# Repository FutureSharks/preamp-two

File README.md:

# Preamp Two

Here is my Hi-Fi preamplifier project. In this repository you can find schematics, PCB layouts, CircuitPython code, BoMs, measurements and photos.

Features:

* MDAC volume controller
* 6 way relay based input selector
* High performance design with measurements
* Quality components and modular design
* Completely digitally controlled
* All open source and written in Python

## Components and code

The preamplifier is made up of a number of connected components:

* MDAC attenuator ([PCB](PCBs/mdac-attenuator), [code](code/modules/mdac_attenuator.py)): Controls the volume
* Input selector ([PCB](PCBs/input-selector), [code](code/modules/input_selector.py)): Selects the input
* Encoder panel ([PCB](PCBs/encoder-panel), [code](code/modules/encoder_panel.py)): Holds rotary encoder and LED indicator ring
* Power Supply 5V ([PCB](PCBs/psu-digital)): Power supply for digital components.
* Power Supply +/- 15V ([PCB](PCBs/psu-analog)): Analog Power supply for MDAC attenuator
* Micro controller board ([PCB](PCBs/mcu-board), [code](code/main.py)): Holds the [Itsy Bitsy M4 Express](https://learn.adafruit.com/introducing-adafruit-itsybitsy-m4?view=all) and other connectors
* RCA panel ([PCB](PCBs/rca-panel)): For the RCA sockets and connectors

The PCBs and schematics were created in [KiCad](http://kicad.org/) and the code that runs on the micro controller is [CircuitPython](https://circuitpython.org/).

## Enclosure

Diagrams, CAD files and other information can be found here: [enclosure](enclosure)

## Measurements

THD, S/N ratio and power consumption: [measurements](measurements)

## Prototypes and testing

See here for a number of different [prototypes](prototypes). All PCBs were made by [OSH Park](https://oshpark.com/).

## Photos

---

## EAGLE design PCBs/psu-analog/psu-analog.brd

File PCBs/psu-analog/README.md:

# Analog Power Supply

This the +/- 15V power supply. It powers the op-amp in the MDAC attenuator using TPS7A3301 regulators.

The PCB files are in Eagle format.

## Photos

## Schematic

## Layout

## BoM

|  Part name | RS part          | Farnell Part | Mouser Part          | Description                                                     | EVM Part name | Notes                |
| ---------- | ---------------- | ------------ | -------------------- | --------------------------------------------------------------- | ------------- | -------------------- |
| C1/C2      | 571319           |              | 667-EEU-FC1V182S     | Large input cap, 7.5mm/18mm                                     | -             |                      |
| C5/C6      | -                |              | 80-C1206C104K5R      | 1206, 0.1uF, X5R or X7R                                         | -             |                      |
| C7/C8      | 7900610          |              | 81-GRM31CR61H106KA2L | 1206, 47uF, X5R or X7R, 2220 package                            | C1            |                      |
| C3A/B      | 7236657          |              | 81-GRM31MR71H105KA88 | 1206, 1uF, X5R or X7R                                           | C3            | NR/SS                |
| C4A/B      | 2644141          |              | 80-C1206C103K1R      | 1206, 10nF/0.01uF, X5R or X7R                                   | C4            | CFF/CBYP             |
| C9-14      | 7900610          |              | 81-GRM31CR61H106KA2L | 1206, 22-15uF, multiple, 2220 package                           | C5-C9         | Total at least 47uF  |
| C15/C16    | 571408 or 571290 |              | 667-EEU-FC1E102      | Large output cap, 5mm/13mm                                      | C10           |                      |
| R1A/B      |                  |              | 667-ERJ-8ENF1244V    | 1.24M                                                           | R1            | Value for -15VDC     |
| R2A/B      |                  |              | 667-ERJ-8ENF1053V    | 105K                                                            | R2            | Value for -15VDC     |
| B1/2       | 8148800          | 1336500      | 625-DFL1508S-E3/77   | VISHAY - DFL1508S-E3/45, BRIDGE RECTIFIER                       |               |                      |
| IC1/IC2    |                  |              | 595-TPS7A3301KC      | LDO Voltage Regulators -3 to -36V,-1A,Ultra Low Noise,High PSRR |               |                      |
| TR1        | 2239216          |              |                      | Block FL6/FL8, Talema/Amveco 5/7VA or standard EI-42            |               |                      |
| F1         | 7874164          |              | 576-64900001039      | 5x20mm Fuseholder 6.3A 250V                                     |               |                      |
| AC         | 403932           |              |                      | 5.08mm Pitch 2 Way 1 Row Straight PCB Header                    |               | AC in                |
| KK1/KK2    |                  |              | 532-513002B25G       |                                                                 |               | Heatsinks, SK104-PAD |
| LED        | -                | -            | -                    | Any 1206 LED                                                    |               |                      |
| RLED       | -                | -            | -                    | To match LEDs                                                   |               |                      |
| X2         |                  |              |                      |                                                                 |               | Power out            |
| Fuse       |                  |              | 530-5ST63-R          | 5x20mm, 63mA                                                    |               |                      |

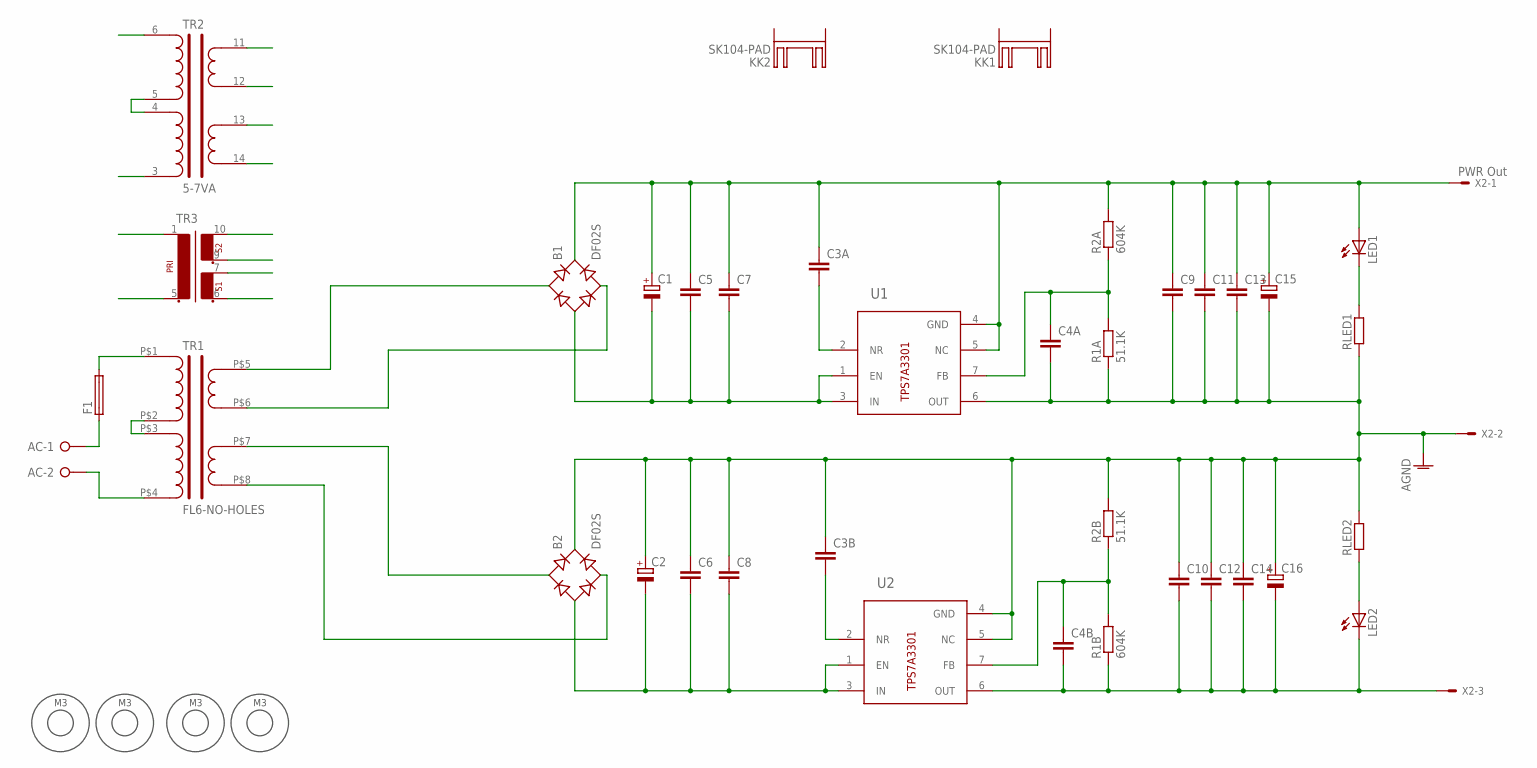
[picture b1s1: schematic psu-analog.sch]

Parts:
AC: W237-02P; W237-132
B1, B2: DF02S; DFS
C1, C2: CPOL-EUE7.5-18; E7,5-18
C3A, C3B, C4A, C4B, C5, C6, C7, C8, C9, C10, C11, C12, C13, C14: C-EUC1206; C1206
C15, C16: CPOL-EUE5-13; E5-13
F1: GSH15
KK1, KK2: SK104-PAD
LED1, LED2: LEDSMT1206; 1206
R1A, R2B: 51.1K; R1206
R1B, R2A: 604K; R1206
RLED1, RLED2: R-EU_R1206; R1206
TR1: FL6-NO-HOLES
TR2: 5-7VA; 5_7VA-PC
TR3: EI42-2
U1, U2: TPS7A3301KC-OTHER-PACKAGE; 7TO-220-OTHER
U$1, U$2, U$3, U$4: M3_HOLE
X2: PWR Out; 22-23-2031

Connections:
AGND: B2.+, C2.+, C3B.1, C4A.2, C6.1, C8.1, C9.2, C10.1, C11.2, C12.1, C13.2, C14.1, C15.-, C16.+, R1A.1, R2B.2, RLED1.1, RLED2.2, U1.6 (OUT), U2.4 (GND), U2.5 (NC), X2.2
unnamed: TR1.P$2 (PRI1B), TR1.P$3 (PRI2A), TR2.4, TR2.5
unnamed: F1.2, TR1.P$1 (PRI1A), TR2.6, TR3.1
unnamed: AC.2, TR1.P$4 (PRI2B), TR2.3, TR3.5 (2)
unnamed: AC.1, F1.1
unnamed: LED2.A, RLED2.1
unnamed: LED1.C, RLED1.2
unnamed: C4A.1, R1A.2, R2A.1, U1.7 (FB)
unnamed: C3B.2, U2.2 (NR)
unnamed: C4B.1, R1B.2, R2B.1, U2.7 (FB)
unnamed: B1.AC2, TR1.P$6 (SEC1B), TR2.12, TR3.9 (5)
unnamed: B1.AC1, TR1.P$5 (SEC1A), TR2.11, TR3.10 (6)
unnamed: B2.AC2, TR1.P$8 (SEC2B), TR2.14, TR3.6 (3)
unnamed: C3A.2, U1.2 (NR)
unnamed: B2.AC1, TR1.P$7 (SEC2A), TR2.13, TR3.7 (4)
unnamed: C4B.2, C10.2, C12.2, C14.2, C16.-, LED2.C, R1B.1, U2.6 (OUT), X2.3
unnamed: B1.+, C1.+, C3A.1, C5.1, C7.1, C9.1, C11.1, C13.1, C15.+, LED1.A, R2A.2, U1.4 (GND), U1.5 (NC), X2.1
VIN+: B1.-, C1.-, C5.2, C7.2, U1.1 (EN), U1.3 (IN)
VIN-: B2.-, C2.-, C6.2, C8.2, U2.1 (EN), U2.3 (IN)

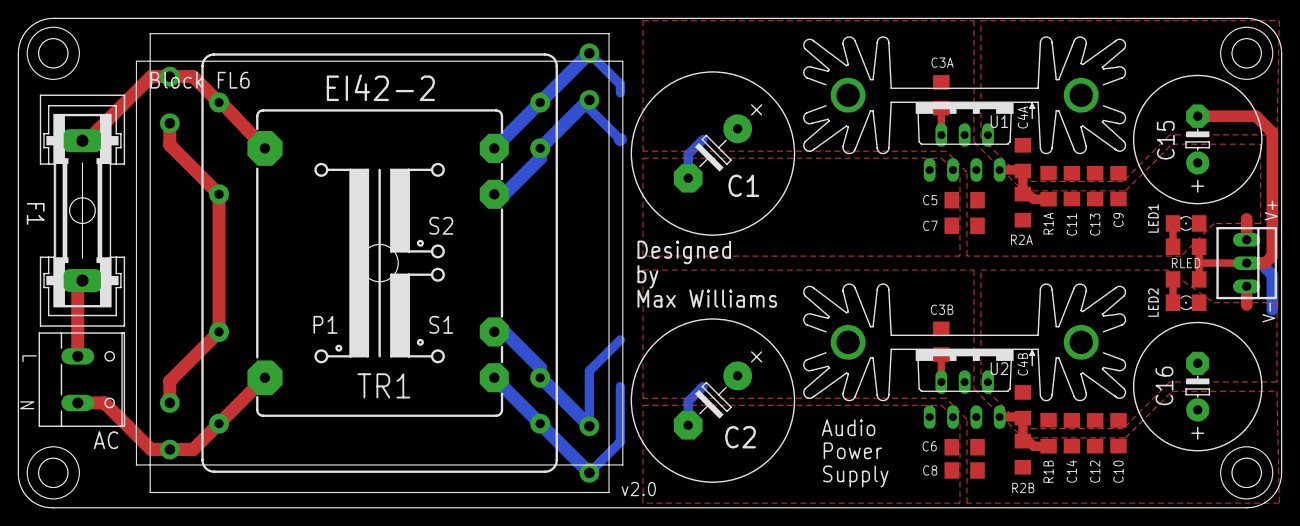
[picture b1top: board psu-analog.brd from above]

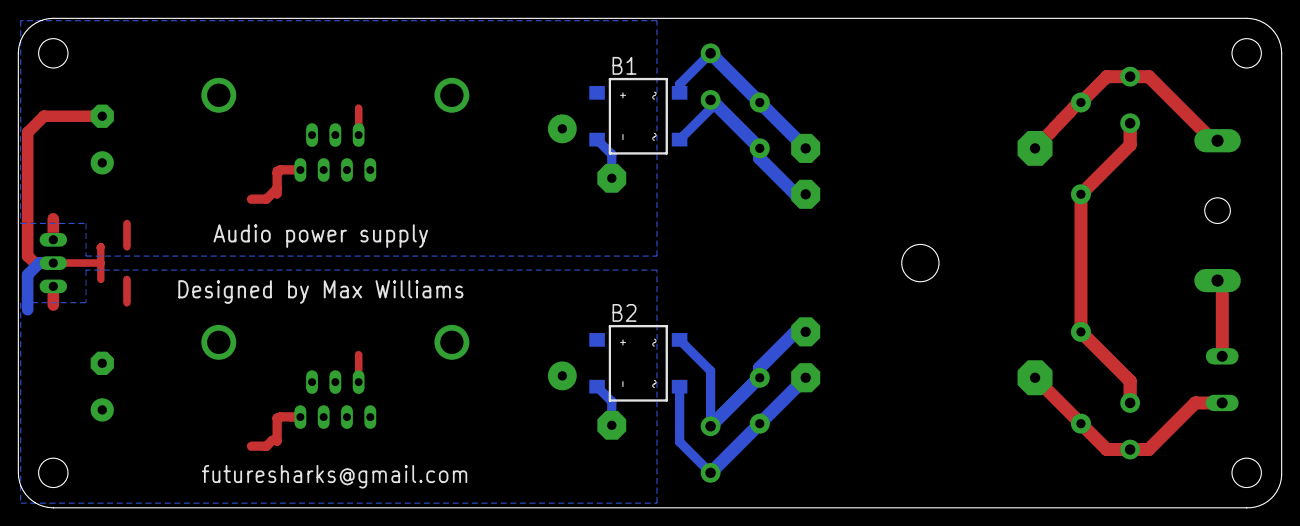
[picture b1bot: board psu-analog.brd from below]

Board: 2 copper layers, 137.7 x 53.3 mm, 42 parts (2 on the bottom side), 19 nets.

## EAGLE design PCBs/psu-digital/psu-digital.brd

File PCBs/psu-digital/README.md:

# Digital Power Supply

This the 5V digital power supply. It powers the input selector, digital part of the MDAC attenuator, the NeoPixels in the encoder panels and the encoders.

It uses a LT1763 regulator.

The PCB files are in Eagle format.

## Photos

## Schematic

## Layout

## BoM

| Reference   | Footprint / Notes  |
|-------------|--------------------|
| F1 | Fuse holder. |
| TR1 | Pads for Block FL2/FL4/FL6/FL8 or EI38 or EI30. Ideally 2x 6VAC. |
| B1 | VISHAY DFL1508S bridge rectifier. |
| C1 | Panasonic FC 1500UF, 16V. |
| L1 | INDUCTOR, 1210 CASE, 10UH. |
| L2 | FERRITE BEAD, 0.1OHM, 2A, 1206. |
| C2 | 100nF X7R, 1206 package. |
| IC1 | LT1763CS8-5, 5V fixed regulator. |
| C3 | C0G/NP0, 10NF, 100V, 1206 package. |
| C4 | Panasonic FK 100UF, 6.3V, SMD. |
| C5 | 100nF X7R, 1206 package. |
| R1 | Resistor for LED, 1206 package. |
| LED | 1206 LED |

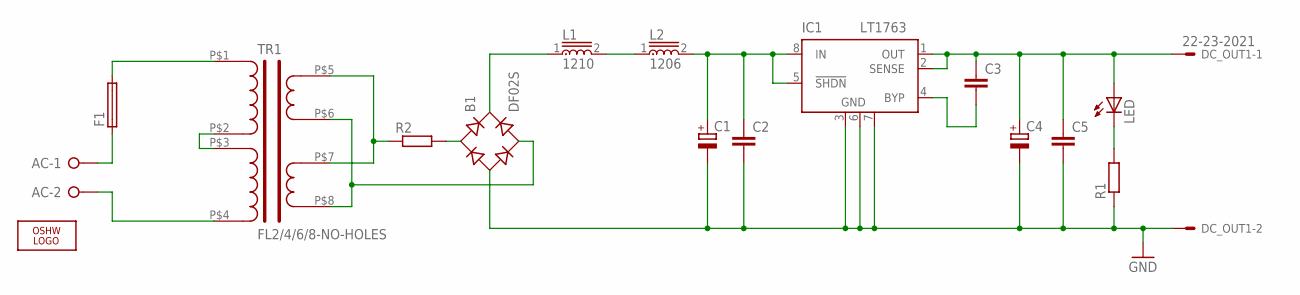
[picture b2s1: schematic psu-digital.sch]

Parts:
AC: W237-02P; W237-132
B1: DF02S; DFS
C1: CPOL-EUE7.5-16; E7,5-16
C2, C3, C5: C-EUC1206; C1206
C4: CPOL-EUD; PANASONIC_D
DC_OUT1: 22-23-2021
F1: GSH15
IC1: LT1763; SOIC8
L1: 1210
L2: 1206
LED: LEDCHIPLED_1206; CHIPLED_1206
LOGO1: OSHW_LOGO_FILLX0200-NT; OSHW_FILLX200_NOTEXT
R1: R-EU_R1206; R1206
R2: R-EU_R1210; R1210
TR1: FL2/4/6/8-NO-HOLES

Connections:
GND: B1.-, C1.-, C2.2, C4.-, C5.2, DC_OUT1.2, IC1.3 (GND), IC1.6 (GND), IC1.7 (GND), R1.1
unnamed: TR1.P$2 (PRI1B), TR1.P$3 (PRI2A)
unnamed: F1.2, TR1.P$1 (PRI1A)
unnamed: AC.2, TR1.P$4 (PRI2B)
unnamed: AC.1, F1.1
unnamed: R2.1, TR1.P$5 (SEC1A), TR1.P$7 (SEC2A)
unnamed: B1.AC1, R2.2
unnamed: C3.2, IC1.4 (BYP)
unnamed: LED.C, R1.2
unnamed: B1.+, L1.1
unnamed: C3.1, C4.+, C5.1, DC_OUT1.1, IC1.1 (OUT), IC1.2 (SENSE), LED.A
unnamed: L1.2, L2.1
unnamed: B1.AC2, TR1.P$6 (SEC1B), TR1.P$8 (SEC2B)
unnamed: C1.+, C2.1, IC1.5 (!SHDN), IC1.8 (IN), L2.2

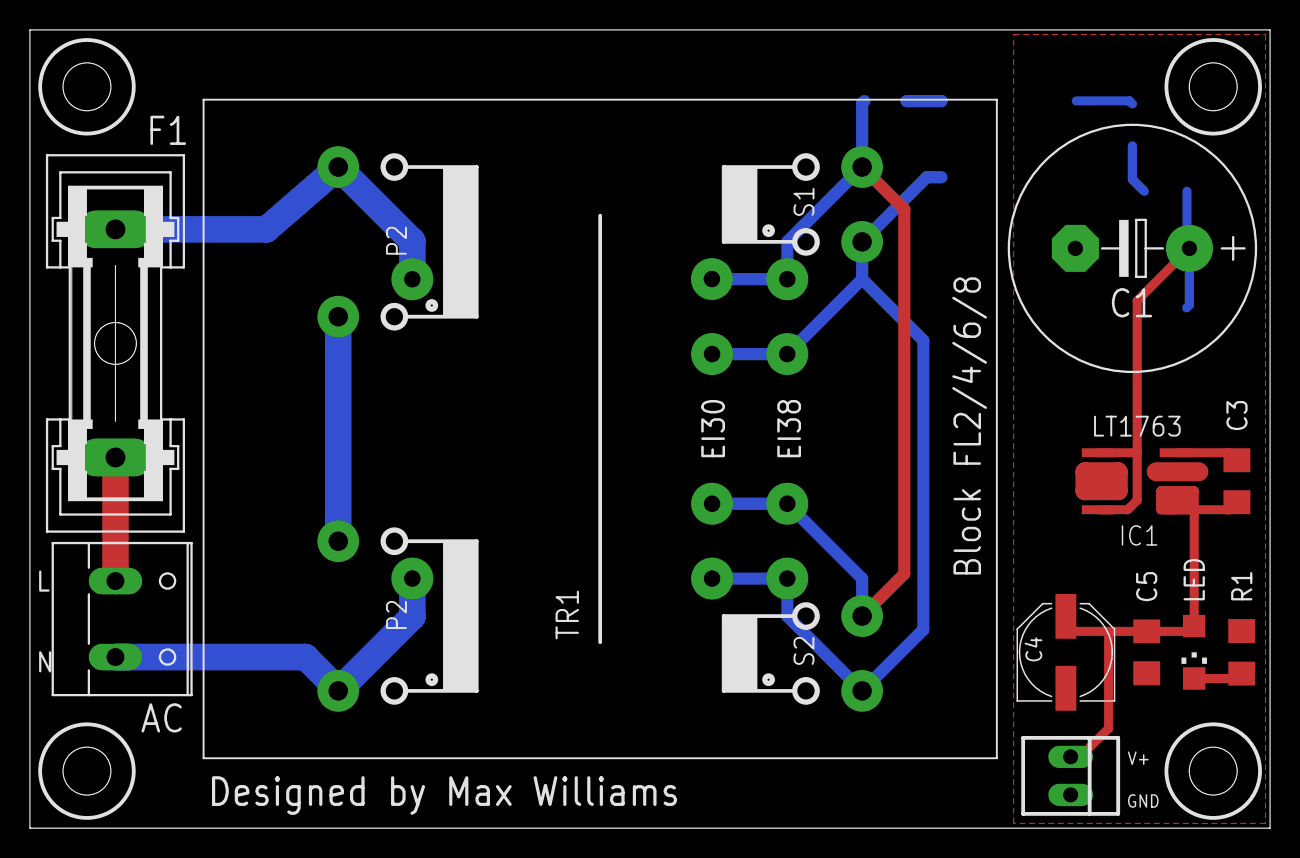
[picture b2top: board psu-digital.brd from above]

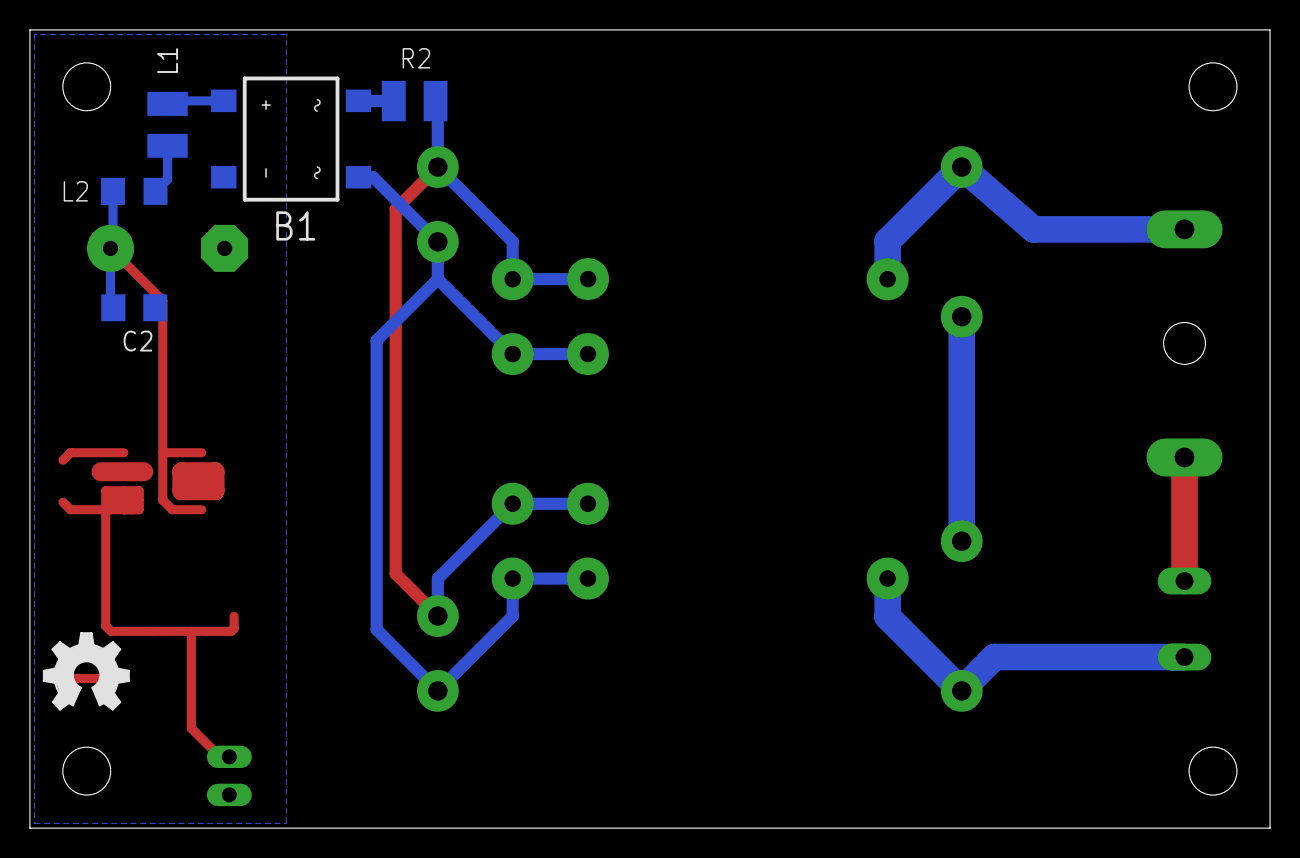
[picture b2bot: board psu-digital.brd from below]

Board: 2 copper layers, 82.9 x 53.3 mm, 17 parts (6 on the bottom side), 14 nets.

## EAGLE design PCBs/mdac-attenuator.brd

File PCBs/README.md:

# PCBs and schematics

* [MDAC attenuator](mdac-attenuator): A digital attenuator
* [Input selector](input-selector): Relay based input selector
* [Encoder panel](encoder-panel): Holds rotary encoder and LED ring
* [Power Supply 5V](psu-digital): Power supply for digital components.
* [Power Supply +/- 15V](psu-analog): Power supply for MDAC attenuator
* [Micro controller board](mcu-board): Holds the micro controller and other connectors
* [RCA panel](rca-panel): For the RCA sockets and connectors

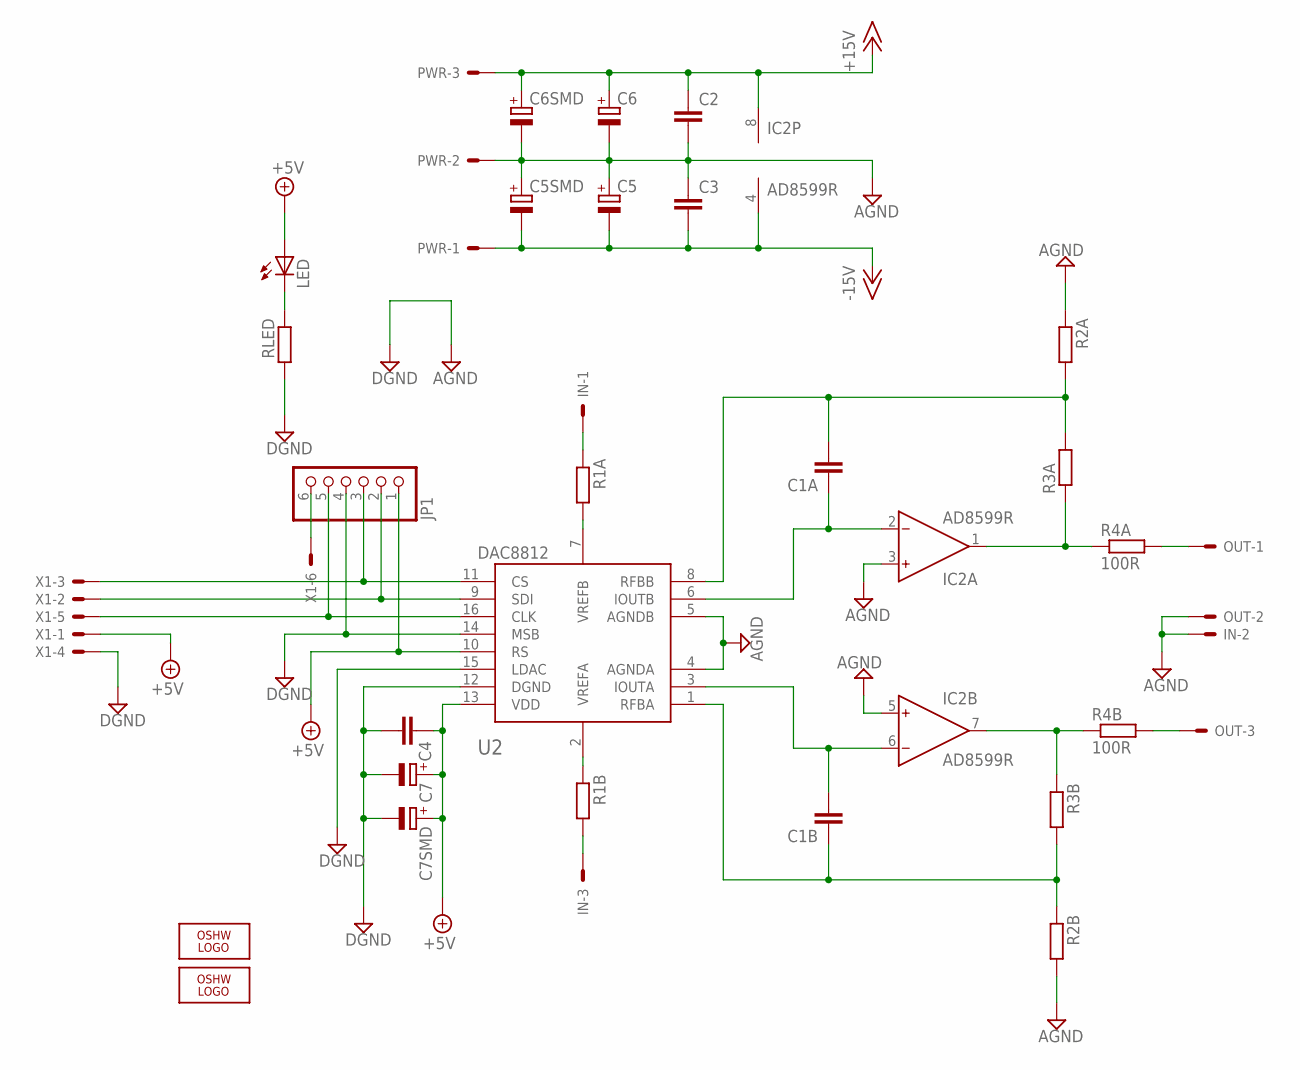
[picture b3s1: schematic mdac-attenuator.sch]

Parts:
C1A, C1B: C-EUC0805; C0805
C2, C3, C4: C-EUC1206; C1206
C5, C6, C7: CPOL-EUE3.5-8; E3,5-8
C5SMD, C6SMD: CPOL-EUE; PANASONIC_E
C7SMD: CPOL-EUD; PANASONIC_D
IC2: AD8599R; SO8
IN: 22-23-2031
JP1: PINHD-1X6; 1X06
LED: LEDSMT1206; 1206
LOGO1, LOGO2: OSHW_LOGO_FILLX0200-NT; OSHW_FILLX200_NOTEXT
OUT: 22-23-2031
PWR: 22-23-2031
R1A, R1B, R2A, R2B, R3A, R3B: R-EU_R1206; R1206
R4A, R4B: 100R; R1206
RLED: R-EU_R1206; R1206
U2: DAC8812; TSSOP16
X1: 22-23-2061

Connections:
+5V: C4.1, C7.+, C7SMD.+, JP1.1, LED.A, U2.10 (RS), U2.13 (VDD), X1.1
+15V: C2.1, C6.+, C6SMD.+, IC2.8 (V+), PWR.3
-15V: C3.2, C5.-, C5SMD.-, IC2.4 (V-), PWR.1
AGND: C2.2, C3.1, C4.2, C5.+, C5SMD.+, C6.-, C6SMD.-, C7.-, C7SMD.-, IC2.3 (IN+), IC2.5 (IN+), IN.2, JP1.4, OUT.2, PWR.2, R2A.1, R2B.2, RLED.2, U2.4 (AGNDA), U2.5 (AGNDB), U2.12 (DGND), U2.14 (MSB), U2.15 (LDAC), X1.4
CLK: JP1.5, U2.16 (CLK), X1.5
CS: JP1.3, U2.11 (CS), X1.3
INL: IN.1, R1A.1
INR: IN.3, R1B.2
unnamed: C1A.1, IC2.2 (IN-), U2.6 (IOUTB)
unnamed: C1B.2, IC2.6 (IN-), U2.3 (IOUTA)
unnamed: R1B.1, U2.2 (VREFA)
unnamed: IC2.7 (OUT), R3B.1, R4B.1
unnamed: JP1.6, X1.6
unnamed: LED.C, RLED.1
unnamed: IC2.1 (OUT), R3A.1, R4A.1
unnamed: R1A.2, U2.7 (VREFB)
unnamed: C1A.2, R2A.2, R3A.2, U2.8 (RFBB)
unnamed: C1B.1, R2B.1, R3B.2, U2.1 (RFBA)
OUTL: OUT.1, R4A.2
OUTR: OUT.3, R4B.2
SDI: JP1.2, U2.9 (SDI), X1.2

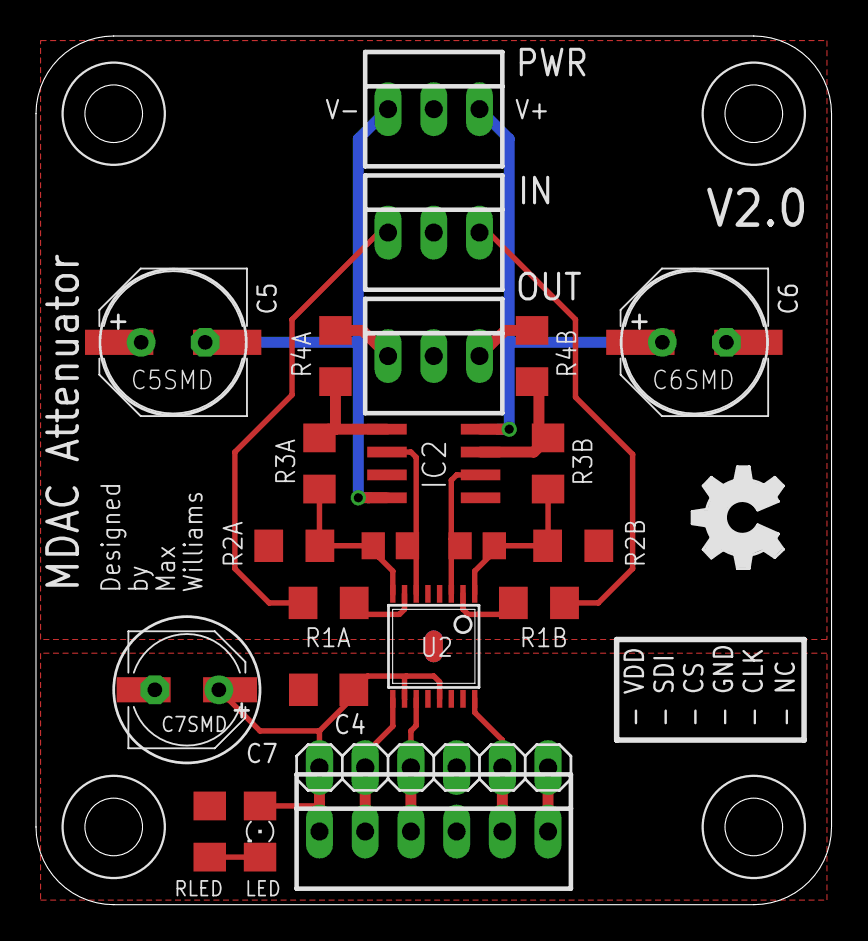
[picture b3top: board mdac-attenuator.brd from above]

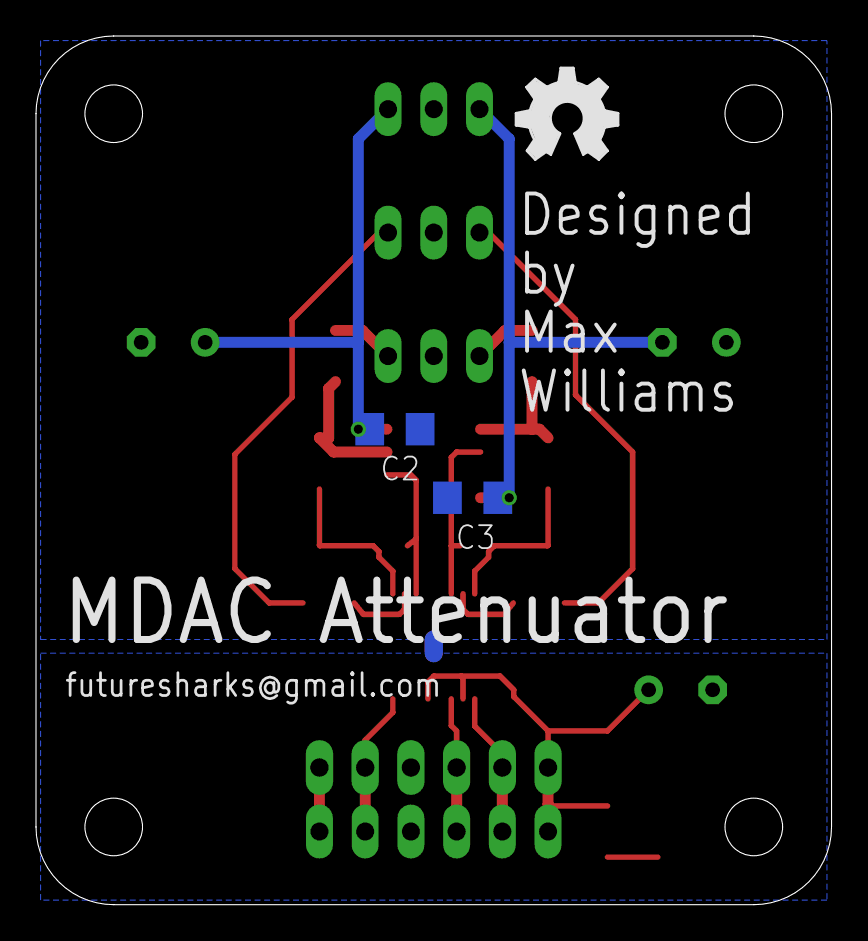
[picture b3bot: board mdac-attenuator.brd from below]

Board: 2 copper layers, 44.2 x 48.3 mm, 34 parts (3 on the bottom side), 21 nets.

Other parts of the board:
U$1, U$2, U$3, U$4: M3_HOLE

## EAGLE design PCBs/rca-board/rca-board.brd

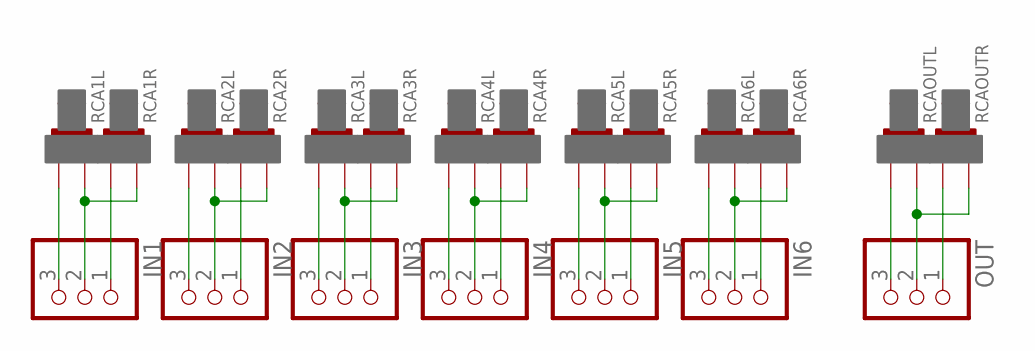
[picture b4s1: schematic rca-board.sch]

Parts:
IN1, IN2, IN3, IN4, IN5, IN6: PINHD-1X3; 1X03
OUT: PINHD-1X3; 1X03
RCA1L, RCA1R, RCA2L, RCA2R, RCA3L, RCA3R, RCA4L, RCA4R, RCA5L, RCA5R, RCA6L, RCA6R: CMC_RCA816; CMC_RCA_816
RCAOUTL: CMC_RCA816; CMC_RCA_816
RCAOUTR: CMC_RCA816; CMC_RCA_816

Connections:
GND1: IN1.2, RCA1L.GND, RCA1R.GND
GND2: IN2.2, RCA2L.GND, RCA2R.GND
GND3: IN3.2, RCA3L.GND, RCA3R.GND
GND4: IN4.2, RCA4L.GND, RCA4R.GND
GND5: IN5.2, RCA5L.GND, RCA5R.GND
GND6: IN6.2, RCA6L.GND, RCA6R.GND
GNDOUT: OUT.2, RCAOUTL.GND, RCAOUTR.GND
unnamed: IN2.3, RCA2L.SIGNAL
unnamed: IN1.3, RCA1L.SIGNAL
unnamed: IN3.3, RCA3L.SIGNAL
unnamed: IN2.1, RCA2R.SIGNAL
unnamed: IN4.3, RCA4L.SIGNAL
unnamed: IN3.1, RCA3R.SIGNAL
unnamed: IN5.3, RCA5L.SIGNAL
unnamed: IN4.1, RCA4R.SIGNAL
unnamed: IN6.3, RCA6L.SIGNAL
unnamed: IN5.1, RCA5R.SIGNAL
unnamed: OUT.1, RCAOUTR.SIGNAL
unnamed: IN6.1, RCA6R.SIGNAL
unnamed: IN1.1, RCA1R.SIGNAL
unnamed: OUT.3, RCAOUTL.SIGNAL

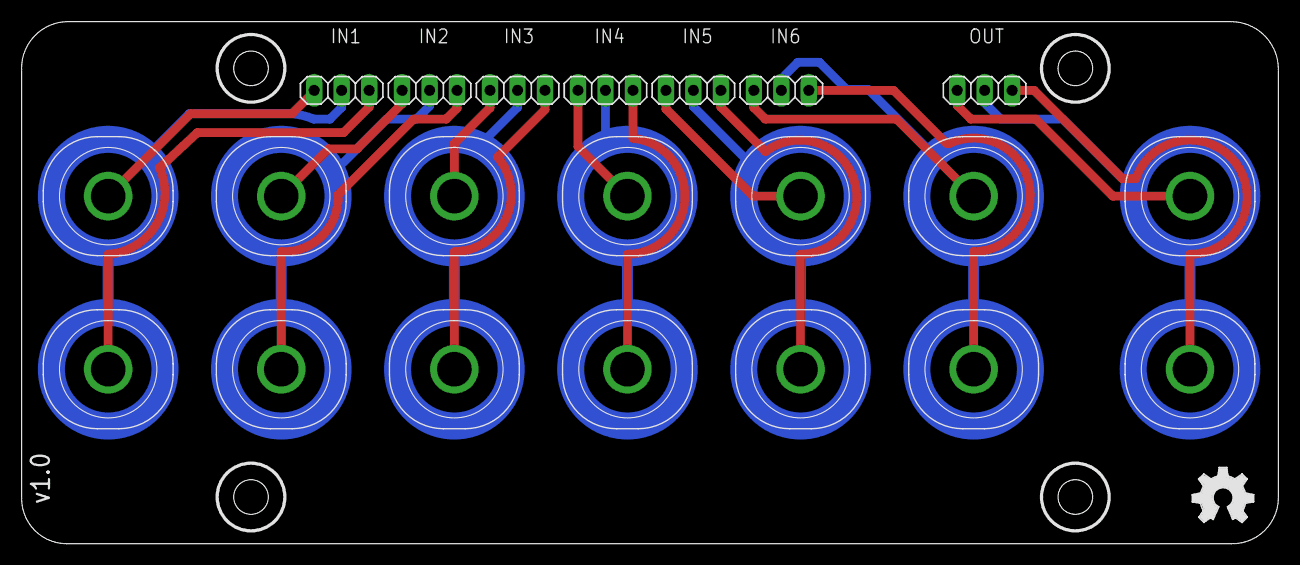
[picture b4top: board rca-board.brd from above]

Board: 2 copper layers, 116.2 x 48.3 mm, 23 parts (1 on the bottom side), 21 nets.

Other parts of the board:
LOGO1, LOGO2: OSHW_LOGO_FILLX0200-NT; OSHW_FILLX200_NOTEXT

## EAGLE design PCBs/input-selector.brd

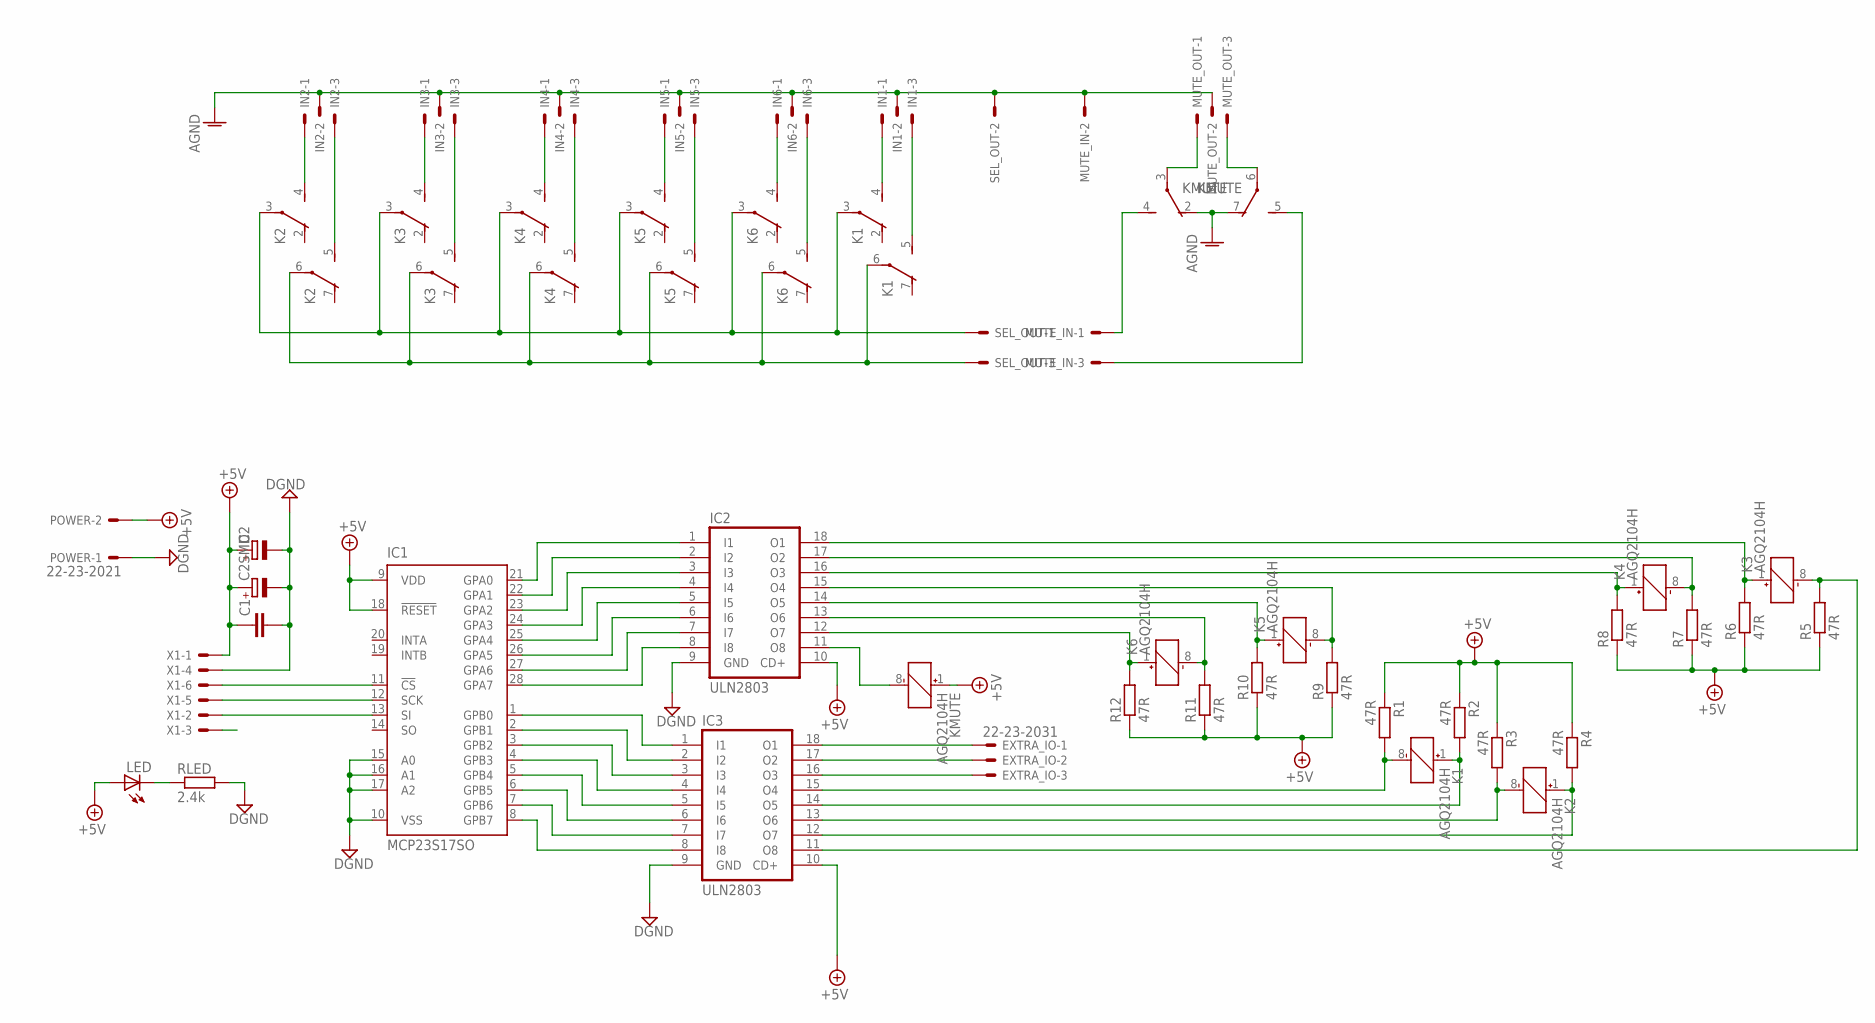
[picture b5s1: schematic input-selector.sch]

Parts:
C1: C-EUC1206; C1206
C2: CPOL-EUE3.5-8; E3,5-8
C2SMD: CPOL-EUE; PANASONIC_E
EXTRA_IO: 22-23-2031
IC1: MCP23S17SO; SO28W
IC2, IC3: ULN2803; SO-18W
IN1, IN2, IN3, IN4, IN5, IN6: 22-23-2031
K1, K2, K3, K4, K5, K6: AGQ2104H; PCBBOARD
KMUTE: AGQ2104H; PCBBOARD
LED: LEDSMT1206; 1206
MUTE_IN: 22-23-2031
MUTE_OUT: 22-23-2031
POWER: 22-23-2021
R1, R2, R3, R4, R5, R6, R7, R8, R9, R10, R11, R12: 47R; R1206
RLED: 2.4k; R1206
SEL_OUT: 22-23-2031
X1: 22-23-2061

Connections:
+5V: C1.1, C2.+, C2SMD.+, IC1.9 (VDD), IC1.18 (!RESET), IC2.10 (CD+), IC3.10 (CD+), KMUTE.1 (+), LED.A, POWER.2, R1.1, R2.1, R3.1, R4.1, R5.1, R6.1, R7.1, R8.1, R9.1, R10.1, R11.1, R12.1, X1.1
AGND: IN1.2, IN2.2, IN3.2, IN4.2, IN5.2, IN6.2, KMUTE.2 (O), KMUTE.7 (O), MUTE_IN.2, MUTE_OUT.2, SEL_OUT.2
CLK: IC1.12 (SCK), X1.5
CS: IC1.11 (!CS), X1.6
DGND: C1.2, C2.-, C2SMD.-, IC1.10 (VSS), IC1.15 (A0), IC1.16 (A1), IC1.17 (A2), IC2.9 (GND), IC3.9 (GND), POWER.1, RLED.2, X1.4
INL: K1.3, K2.3, K3.3, K4.3, K5.3, K6.3, SEL_OUT.1
INR: K1.6, K2.6, K3.6, K4.6, K5.6, K6.6, SEL_OUT.3
unnamed: IN1.1, K1.4 (S)
unnamed: EXTRA_IO.2, IC3.17 (O2)
unnamed: IN1.3, K1.5 (S)
unnamed: EXTRA_IO.3, IC3.16 (O3)
unnamed: IC3.15 (O4), K1.8 (-), R1.2
unnamed: IC2.11 (O8), KMUTE.8 (-)
unnamed: IC1.21 (GPA0), IC2.1 (I1)
unnamed: IC3.14 (O5), K1.1 (+), R2.2
unnamed: IC3.13 (O6), K2.8 (-), R3.2
unnamed: EXTRA_IO.1, IC3.18 (O1)
unnamed: IC2.16 (O3), K4.1 (+), R8.2
unnamed: IC3.12 (O7), K2.1 (+), R4.2
unnamed: IC3.11 (O8), K3.8 (-), R5.2
unnamed: IC2.18 (O1), K3.1 (+), R6.2
unnamed: IC2.15 (O4), K5.8 (-), R9.2
unnamed: IC2.13 (O6), K6.8 (-), R11.2
unnamed: KMUTE.6, MUTE_OUT.3
unnamed: KMUTE.3, MUTE_OUT.1
unnamed: IC2.12 (O7), K6.1 (+), R12.2
unnamed: IC1.23 (GPA2), IC2.3 (I3)
unnamed: IC2.17 (O2), K4.8 (-), R7.2
unnamed: IC2.14 (O5), K5.1 (+), R10.2
unnamed: IN5.1, K5.4 (S)
unnamed: IN5.3, K5.5 (S)
unnamed: IN6.1, K6.4 (S)
unnamed: IN6.3, K6.5 (S)
unnamed: IN2.1, K2.4 (S)
unnamed: IN2.3, K2.5 (S)
unnamed: IN3.1, K3.4 (S)
unnamed: IN3.3, K3.5 (S)
unnamed: IN4.1, K4.4 (S)
unnamed: IN4.3, K4.5 (S)
unnamed: IC1.25 (GPA4), IC2.5 (I5)
unnamed: IC1.27 (GPA6), IC2.7 (I7)
unnamed: IC1.1 (GPB0), IC3.1 (I1)
unnamed: IC1.2 (GPB1), IC3.2 (I2)
unnamed: IC1.3 (GPB2), IC3.3 (I3)
unnamed: IC1.4 (GPB3), IC3.4 (I4)
unnamed: IC1.5 (GPB4), IC3.5 (I5)
unnamed: IC1.6 (GPB5), IC3.6 (I6)
unnamed: IC1.7 (GPB6), IC3.7 (I7)
unnamed: IC1.8 (GPB7), IC3.8 (I8)
unnamed: IC1.22 (GPA1), IC2.2 (I2)
unnamed: IC1.24 (GPA3), IC2.4 (I4)
unnamed: IC1.26 (GPA5), IC2.6 (I6)
unnamed: IC1.28 (GPA7), IC2.8 (I8)
unnamed: LED.C, RLED.1
NC: X1.3
OUTL: KMUTE.4 (S), MUTE_IN.1
OUTR: KMUTE.5 (S), MUTE_IN.3
SDI: IC1.13 (SI), X1.2

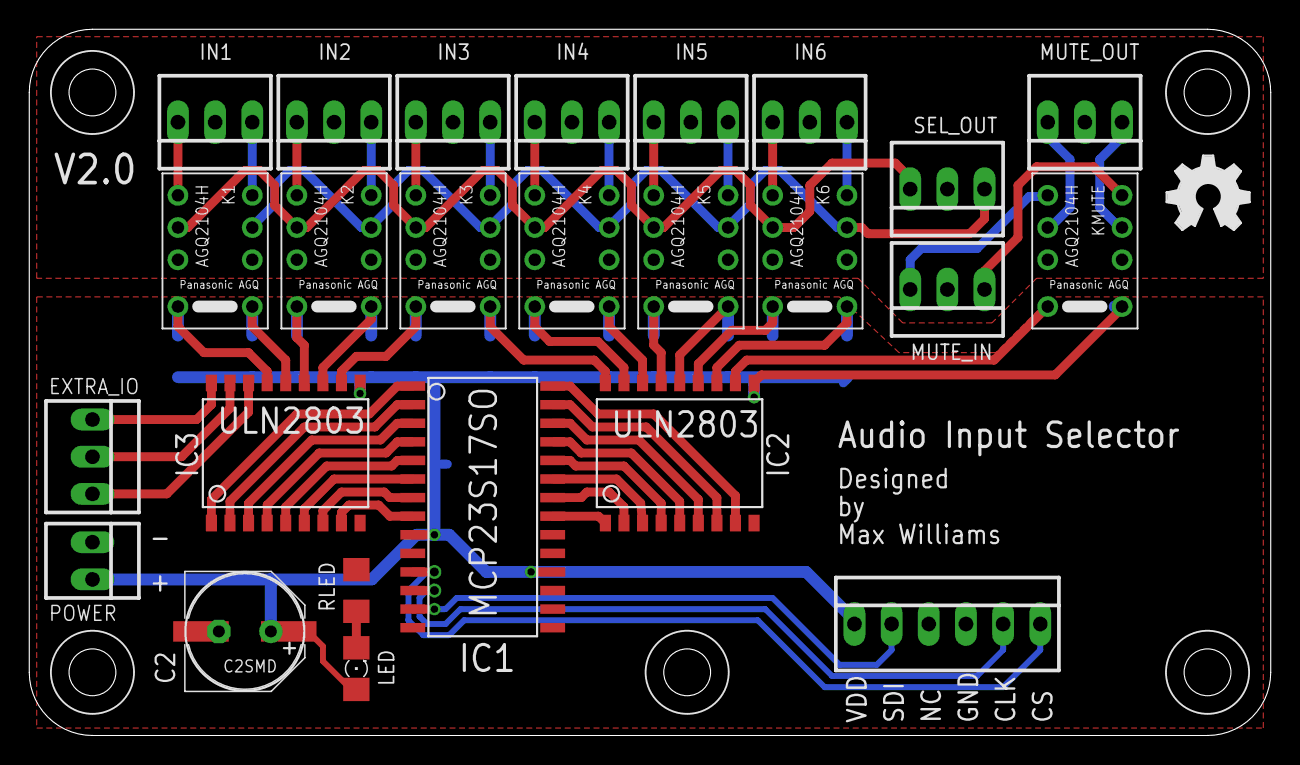
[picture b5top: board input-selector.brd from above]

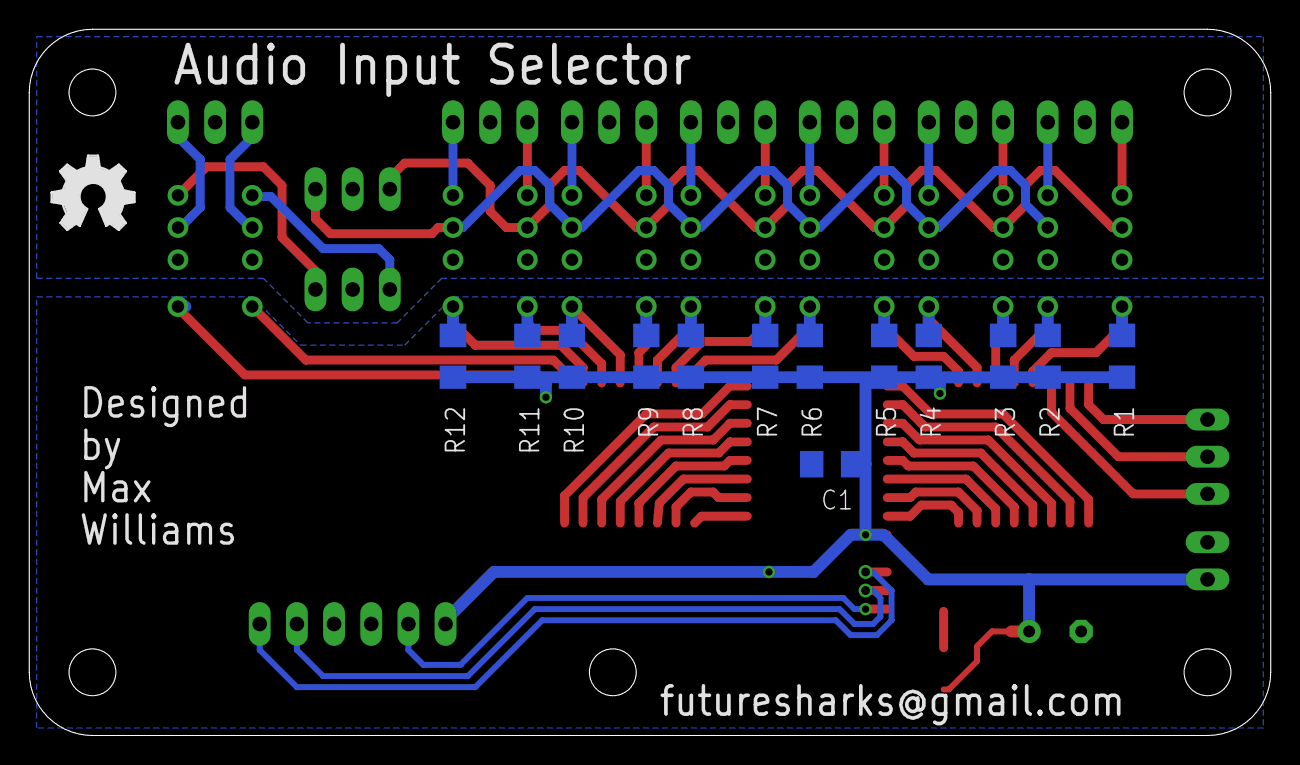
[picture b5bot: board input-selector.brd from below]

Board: 2 copper layers, 84.8 x 48.3 mm, 46 parts (14 on the bottom side), 57 nets.

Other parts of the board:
LOGO1, LOGO2: OSHW_LOGO_FILLX0200-NT; OSHW_FILLX200_NOTEXT
U$1, U$2, U$3, U$4, U$5: M3_HOLE

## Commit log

2016-11-29 Adding BoMs
2018-01-30 Adding gain detail
    misc updates
    Revert "misc updates"
    This reverts commit e2f340ec60ba01b13036b8827b0604f6b8269c83.
2018-12-13 adding more test code Merge remote-tracking branch 'origin/master'
    updates to test code
    measuring time
2018-12-13 Moving code to new dir
2018-12-13 Moving test code to new dir
2018-12-13 adding new circuit python modules for each component
2018-12-13 finished circuitpython test code for input selector
2018-12-16 misc fixes for input selector
2018-12-23 adding mdac tester in python
2018-12-28 reorganising PCBs and updating todo
2018-12-29 adding kicad rcs-panel
2018-12-29 update encoder panel
2019-01-01 updating 3 PCBs to kicad
2019-01-03 small input selector update
2019-01-03 Add new text
2019-01-03 Misc updates to 3 PCBs
2019-01-04 updating mcu-board and input selector
2019-01-05 Fixing input selector panasonic relay footprint
2019-01-05 update mcu-board
2019-01-05 Updating all schematics to kicad (#2)
    * adding kicad rcs-panel
    * update encoder panel
    * updating 3 PCBs to kicad
    * small input selector update
    * Add new text
    * Misc updates to 3 PCBs
2019-01-05 Switching relay type to Omron G6J relays
    Since I can't find a source for the others
2019-01-05 Switching relay type to Omron G6J relays (#3)
    Since I can't find a source for the others
2019-01-05 adding BoMs, images and small design updates
2019-01-05 adding BoMs, images and small design updates (#4)
2019-01-06 Updating docs, images etc
2019-01-06 Removing old images
2019-01-06 updating readme and todo
2019-01-08 adding images
2019-01-11 Updating docs, images etc (#5)
    * Updating docs, images etc
2019-01-13 readme updates
2019-01-18 adding digital and analog PSUs
2019-01-22 adding digital and analog PSUs (#6)
2019-01-26 updating PCB after creating new library for newer 805 RCAs
2019-01-26 fix for mounting holes
2019-01-26 New RCA board (#7)
    * updating PCB after creating new library for newer 805 RCAs
    * fix for mounting holes
2019-01-26 Updating mcu-board PCB
2019-01-26 renaming some nets
2019-01-27 starting to fix silkscreen
2019-01-28 readme update
2019-01-28 change pad/mask clearance
2019-01-29 misc updates
2019-01-29 Update RCA panel images
2019-01-29 Addinng PCB for MCU board (#8)
    * Updating mcu-board PCB
    * renaming some nets
    * starting to fix silkscreen
    * change pad/mask clearance
    * misc updates
    * adding images
2019-02-01 misc fixes
2019-02-01 finishing
2019-02-01 tidying up footprints
2019-02-01 removing old libraries
2019-02-01 adding oshpark page break
2019-02-01 updating encoder panel
2019-02-01 renaming symbol to correct name
2019-02-02 Updating encoder panel PCBs (#9)
    * updating encoder panel
    * misc fixes
    * adding oshpark page break
    * renaming symbol to correct name
    * removing old libraries
    * tidying up footprints
2019-03-06 Adding missing BoMs
2019-03-09 adding prototype images
2019-03-09 moving some files
2019-03-17 adding more prototype photos
2019-03-17 updating todo and some code
2019-03-24 code updates for testing
2019-03-24 Misc code fixes, update todo, some readme, (#10)
    * misc fixes
    * code updates for testing
2019-03-27 Updating mcu-board to not use pin 5
2019-03-27 Updating mcu-board to not use pin 5 (#12)
2019-03-29 fixes after testing
2019-03-29 Finishing some code functionality and updating readme
2019-04-02 Finishing some code functionality and updating readme (#11)
    * Finishing some code functionality and updating readme
    * fixes after testing
    * misc updates
    * updates
    * misc updates
    * misc updates
2019-04-11 adding new photos
2019-04-11 adding new photos (#13)
2019-04-12 Adding OSH park link
2019-04-30 getting better
2019-04-30 some working code now
2019-04-30 remove line
2019-04-30 updating images
2019-04-30 MISC
2019-04-30 Adding more images and updating code with a working version (#14)
    * misc updates
    * getting better
    * some working code now
    * updating images
    * remove line
    * MISC
2019-05-01 adding a gif
2019-06-10 add enclosure info
2019-06-10 update bom to m4
2019-06-10 fix MDAC level bug
2019-06-10 switching arrangement of modules
2019-06-10 removing old arduino sketch
2019-06-10 misc changes
2019-06-10 adding ring fading after timeout
2019-06-16 moving dirs outside of images dir
2019-06-16 update todo
2019-06-16 more code changes
2019-06-16 updates to images
2019-06-16 typo in image path
2019-06-16 add prototype image
2019-06-16 add encoder_panel back
2019-06-16 fixing offset calculation
2019-06-25 adding a gif
    add enclosure info
    update bom to m4
    fix MDAC level bug
    switching arrangement of modules
    removing old arduino sketch
    misc changes
2019-07-20 updating 3d files
2019-07-27 switch to use object inheritance for the encoder panel
    to reduce duplicated code
2019-07-27 rewrite of colour calculation
2019-08-01 changing input control LED style
2019-08-10 finally colours working nicely
2019-08-10 fix debug mode
2019-08-10 tidy up
2019-08-10 Switch to use object inheritance for the encoder panel modules (#16)
    * switch to use object inheritance for the encoder panel
    to reduce duplicated code
    * rewrite of colour calculation
    * changing input control LED style
    * finally colours working nicely
    * fix debug mode
2019-08-18 General tidy up
2019-08-18 General tidy up (#17)
2019-09-12 Updating bearing bracket and mute delay
2019-09-13 Updating bearing bracket and mute delay (#18)
2021-11-08 Update README.md
    https://forum.kicad.info/t/warning-avoid-all-links-to-kicad-pcb-org-use-kicad-org/31521/
2021-11-08 Update README.md (#20)
    https://forum.kicad.info/t/warning-avoid-all-links-to-kicad-pcb-org-use-kicad-org/31521/
